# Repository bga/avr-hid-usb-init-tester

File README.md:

Avr attiny2313 soft usb hid "keyboard" for testing bios usb initialization. Device is blinking if bios assign usb endpoint address and continue sending USB SOF (ie bios in alive). 

For testing motherboard bare metal.

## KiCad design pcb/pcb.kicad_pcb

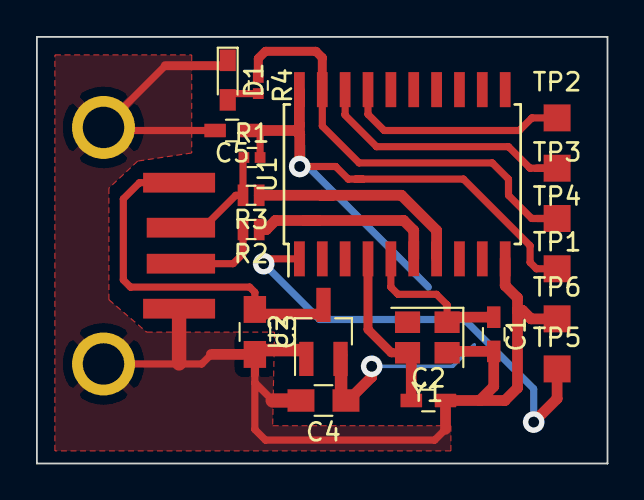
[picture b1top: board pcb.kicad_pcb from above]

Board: 2 copper layers, 31.7 x 23.7 mm, 20 parts (0 on the bottom side), 14 nets.

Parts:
C1, C2: 22pF; C_0603_HandSoldering
C3, C4: 1u; C_0805_HandSoldering
C5: 100n; C_0603_HandSoldering
D1: LED; LED_0603_HandSoldering
J1: USB_A; USB-A-SMT-8231_fix00
R1: 1.5k; R_0402_HandSoldering
R2, R3: 68; R_0402_x2
R4: 1k; R_0402_HandSoldering
TP1, TP2, TP3, TP4, TP5, TP6: TestPoint; Measurement_Point_Square-SMD-Pad_Small
U1: ATtiny2313A-SU; SOIC-20W_7.5x12.8mm_Pitch1.27mm
U2: LM3480-3.3; SOT-23_Handsoldering
Y1: 12MHz; Crystal_SMD_3225-4pin_3.2x2.5mm

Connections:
+3V3: C4.1, C5.1, R1.2, TP1.1, U1.20, U2.2
D+: R2.1, U1.6
D-: R3.1, U1.7
GND: C1.2, C2.2, C3.2, C4.2, C5.2, D1.1, J1.4, J1.5, TP6.1, U1.10, U2.1, Y1.2, Y1.4
unnamed: C1.1, U1.5, Y1.1
unnamed: C2.1, U1.4, Y1.3
unnamed: C3.1, J1.1, U2.3
unnamed: D1.2, R4.2
unnamed: J1.2, R1.1, R3.2
unnamed: J1.3, R2.2
led: R4.1, TP4.1, U1.19
prog-miso: TP3.1, U1.18
prog-mosi: TP2.1, U1.17
prog-reset: TP5.1, U1.1

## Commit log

2022-01-22 1st commit
2022-01-22 + source url
2022-01-22 + change fuses for attiny2313 + change flasher command line - avrdude hardcoded command for downloading flash
2022-01-22 add config.h
2022-01-22 v0.9
2022-02-03 + `StatusLed2` + `Usb_Config_rxCallback` `idleCounterLimit_afterSetup_ms` = 250
2022-05-30 add pcb.kicad_pcb pcb.pro pcb.sch local\ pcb.pretty\ fp-lib-table
2022-09-07 fix dep relations in Makefile
2022-09-07 fix Makefile' clean. rm $(OBJECTS) instead *.o
2022-09-07 + optional SERIAL var (to `SERIAL=COM10 make flash`)
2022-09-07 + optional `USB_CFG_HID_DESC_VER` (default v1.01) + force `USB_CFG_HID_DESC_VER` to 0x0111 (aka v1.11) to work in bios + fix `USB_CFG_INTERFACE_SUBCLASS`. Should be 1, not 0 to work in bios + fix `US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
2022-09-08 cleanup
2022-09-08 add pcb\media\pcb.pdf pcb\media\sch.pdf pcb\media\pcb-real.jpg
2022-09-08 add README.md
